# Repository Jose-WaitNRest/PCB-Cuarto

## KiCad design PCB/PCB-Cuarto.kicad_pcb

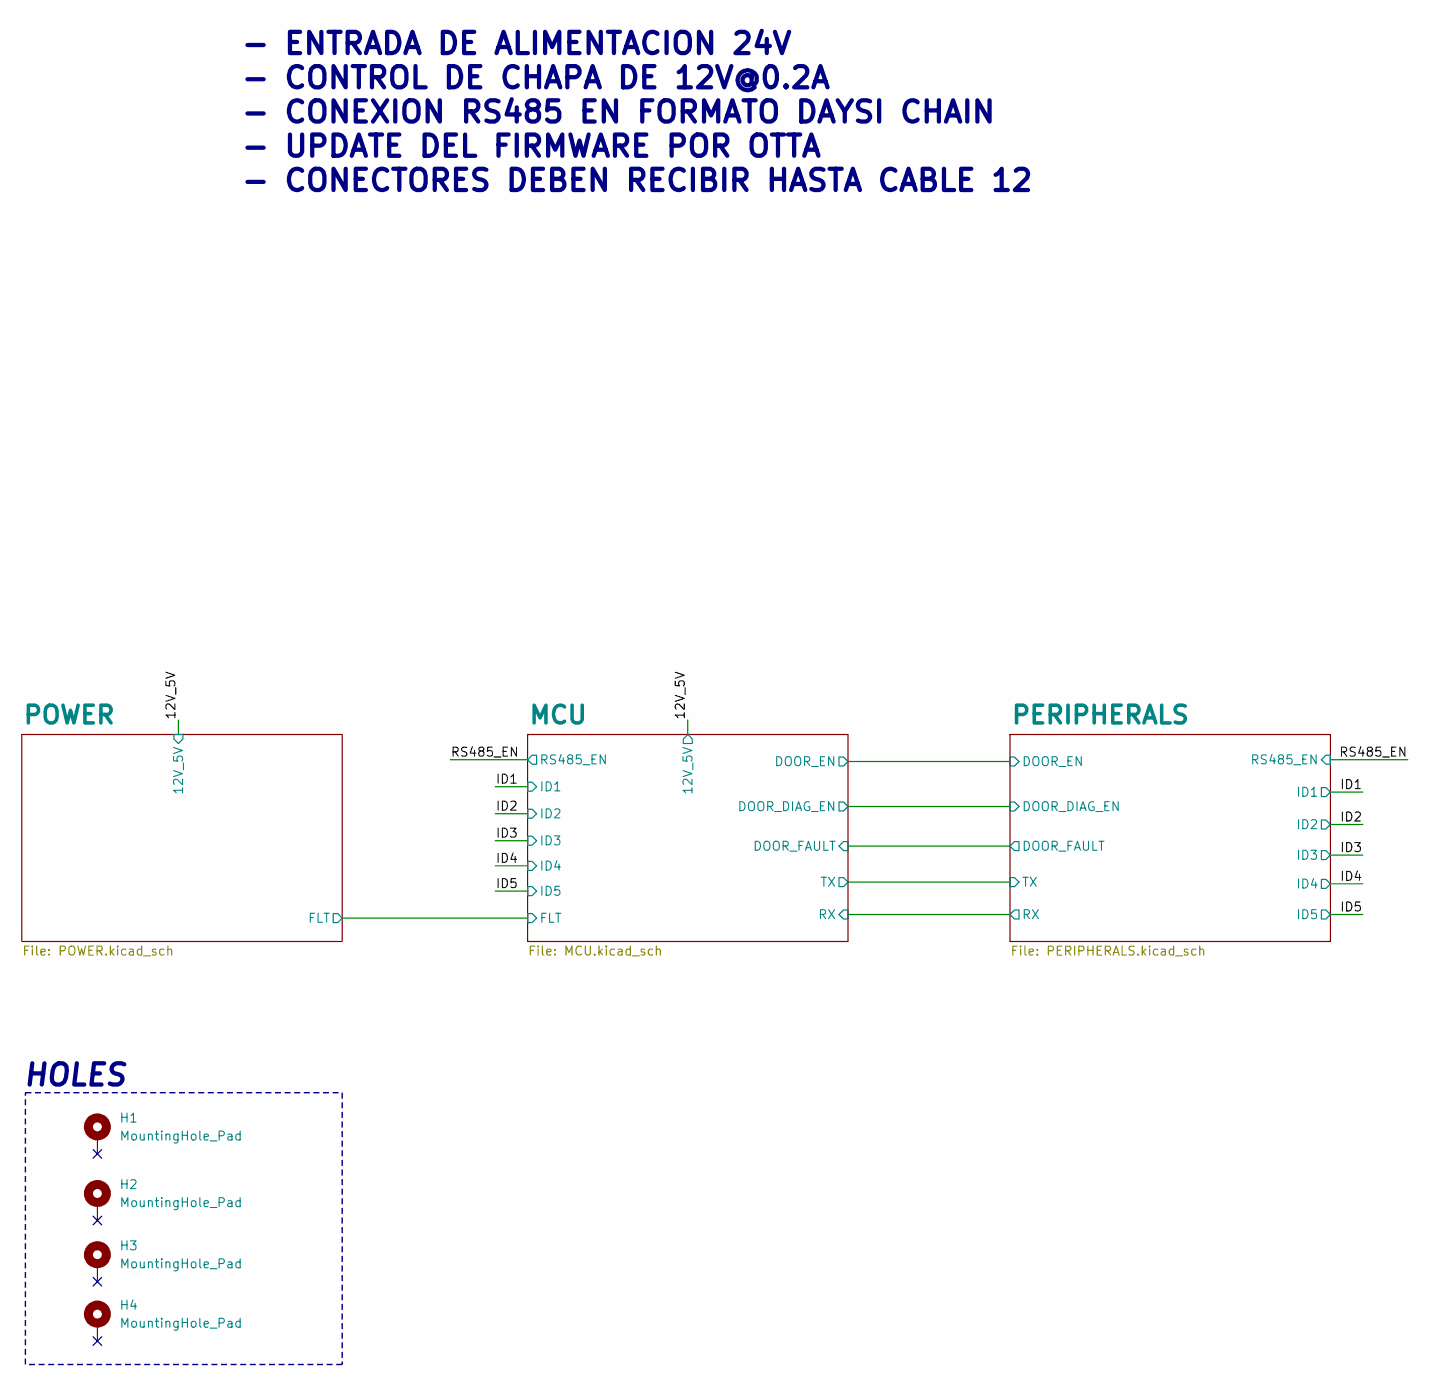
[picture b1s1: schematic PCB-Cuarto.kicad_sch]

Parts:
H1, H2, H3, H4: MountingHole_Pad; MountingHole_3.5mm_Pad_Via

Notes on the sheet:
- ENTRADA DE ALIMENTACION 24V - CONTROL DE CHAPA DE 12V@0.2A - CONEXION RS485 EN FORMATO DAYSI CHAIN - UPDATE DEL FIRMWARE POR OTTA - CONECTORES DEBEN RECIBIR HASTA CABLE 12
HOLES

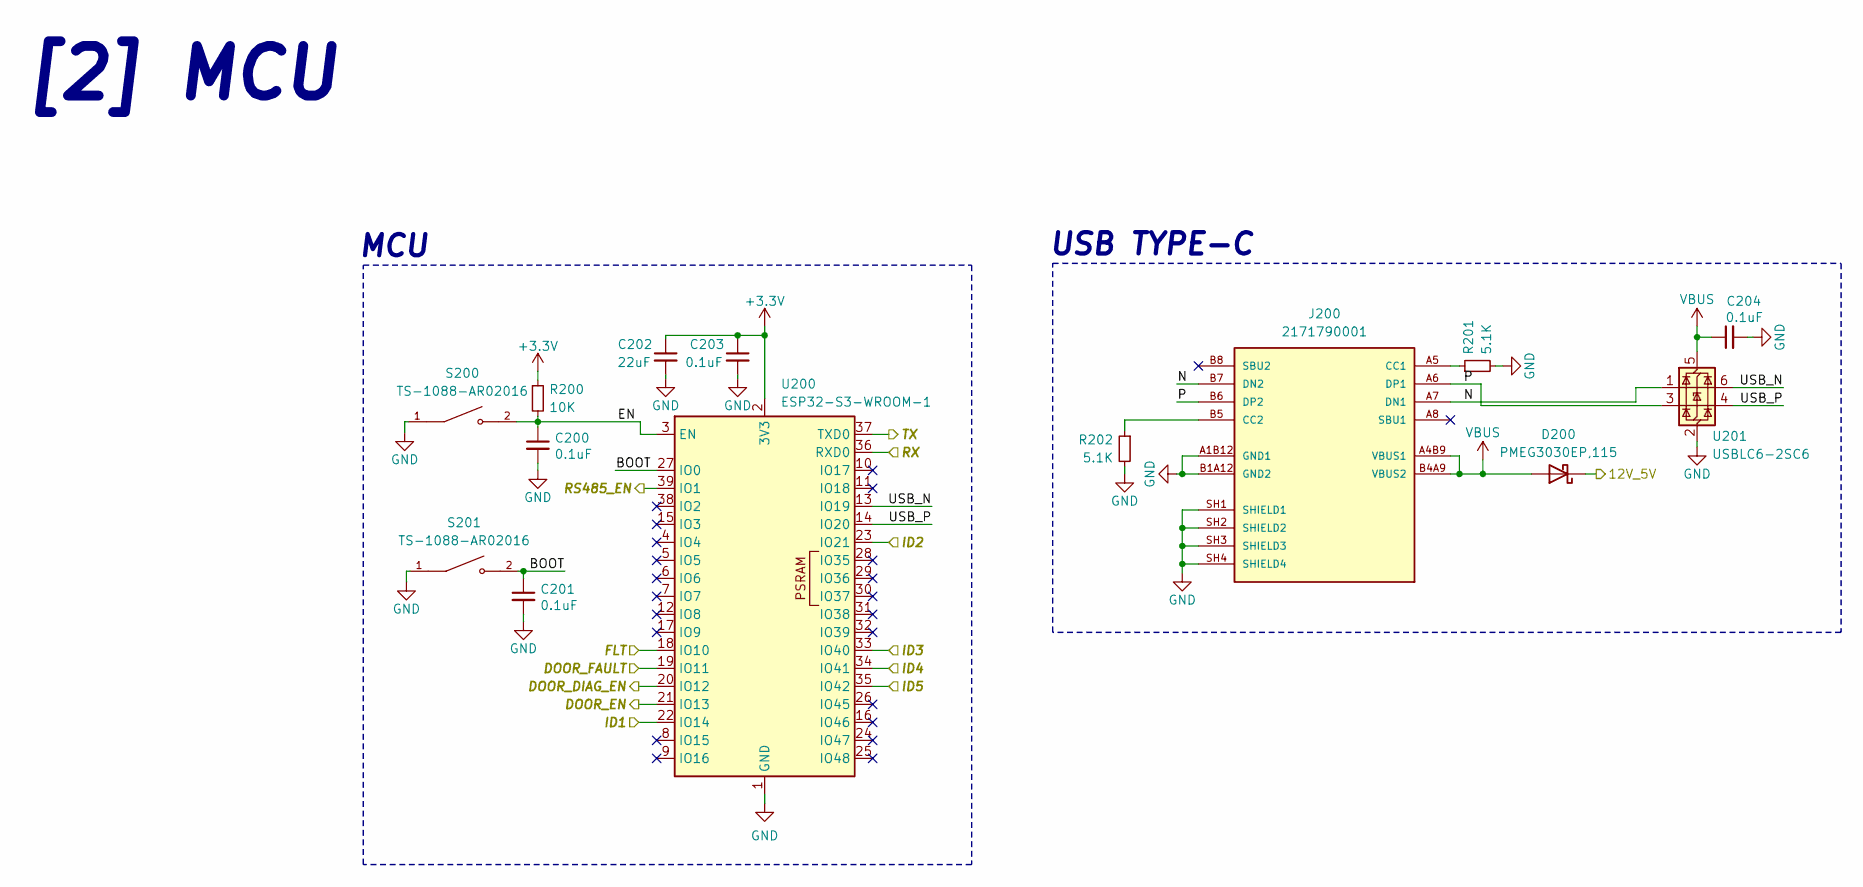
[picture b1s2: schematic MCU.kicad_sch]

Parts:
C200, C201, C203, C204: 0.1uF; C_0603_1608Metric_Pad1.08x0.95mm_HandSolder; LCSC C14663
C202: 22uF; C_0603_1608Metric_Pad1.08x0.95mm_HandSolder; LCSC C86295
D200: PMEG3030EP,115; D_SOD-128; LCSC C255587
J200: 2171790001; MOLEX_2171790001; LCSC C3197684
R200: 10K; R_0603_1608Metric; LCSC C25804
R201, R202: 5.1K; R_0603_1608Metric; LCSC C23186
S200, S201: TS-1088-AR02016; LCSC C720477
U200: ESP32-S3-WROOM-1; LCSC C2913202
U201: USBLC6-2SC6; SOT-23-6

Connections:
+3.3V: C202.1, C203.1, R200.1, U200.2 (3V3); also elsewhere on the board
/12V_5V: D200.1 (K); also elsewhere on the board
/ID1: U200.22 (IO14); also elsewhere on the board
/ID2: U200.23 (IO21); also elsewhere on the board
/ID3: U200.33 (IO40); also elsewhere on the board
/ID4: U200.34 (IO41); also elsewhere on the board
/ID5: U200.35 (IO42); also elsewhere on the board
/MCU/BOOT: C201.1, S201.2, U200.27 (IO0)
/MCU/DOOR_DIAG_EN: U200.20 (IO12); also elsewhere on the board
/MCU/DOOR_EN: U200.21 (IO13); also elsewhere on the board
/MCU/DOOR_FAULT: U200.19 (IO11); also elsewhere on the board
/MCU/EN: C200.1, R200.2, S200.2, U200.3 (EN)
/MCU/FLT: U200.18 (IO10); also elsewhere on the board
/MCU/N: J200.A7 (DN1), J200.B7 (DN2), U201.1 (I/O1)
/MCU/P: J200.A6 (DP1), J200.B6 (DP2), U201.3 (I/O2)
/MCU/RX: U200.36 (RXD0); also elsewhere on the board
/MCU/TX: U200.37 (TXD0); also elsewhere on the board
/MCU/USB_N: U200.13 (IO19), U201.6 (I/O1)
/MCU/USB_P: U200.14 (IO20), U201.4 (I/O2)
/RS485_EN: U200.39 (IO1); also elsewhere on the board
GND: C200.2, C201.2, C202.2, C203.2, C204.2, J200.A1B12 (GND1), J200.B1A12 (GND2), J200.SH1 (SHIELD1), J200.SH2 (SHIELD2), J200.SH3 (SHIELD3), J200.SH4 (SHIELD4), R201.2, R202.2, S200.1, S201.1, U200.1 (GND), U200.40 (GND), U200.41 (GND), U201.2 (GND); also elsewhere on the board
unnamed: J200.A5 (CC1), R201.1
unnamed: J200.B5 (CC2), R202.1
VBUS: C204.1, D200.2 (A), J200.A4B9 (VBUS1), J200.B4A9 (VBUS2), U201.5 (VBUS)

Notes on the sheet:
USB TYPE-C
[2] MCU
MCU

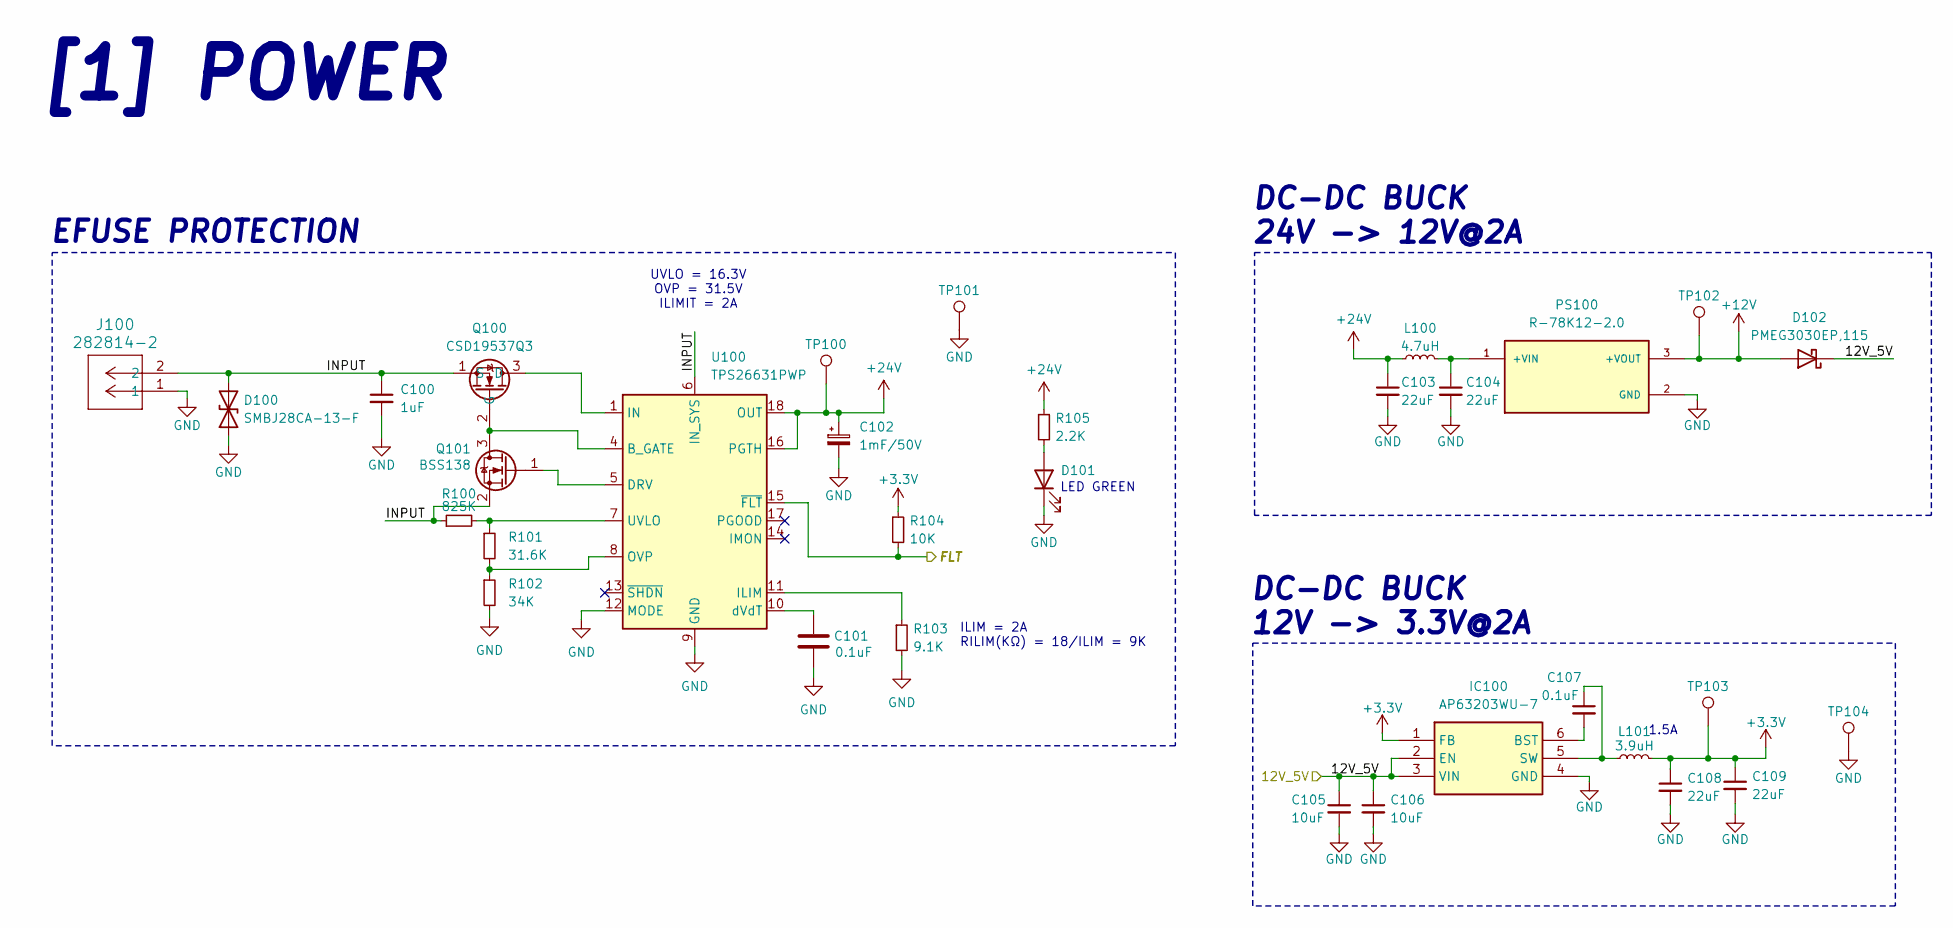
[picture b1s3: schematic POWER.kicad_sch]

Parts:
C100: 1uF; C_1206_3216Metric_Pad1.33x1.80mm_HandSolder; LCSC C1848
C101: 0.1uF; C_0603_1608Metric; LCSC C14663
C102: 1mF/50V; VKMI1701H102MV; LCSC C487374
C103, C104: 22uF; C_1206_3216Metric; LCSC C342620
C105, C106: 10uF; C_0805_2012Metric_Pad1.18x1.45mm_HandSolder; LCSC C440198
C107: 0.1uF; C_0603_1608Metric_Pad1.08x0.95mm_HandSolder; LCSC C14663
C108, C109: 22uF; C_0603_1608Metric_Pad1.08x0.95mm_HandSolder; LCSC C86295
D100: SMBJ28CA-13-F; D_SMB; LCSC C135064
D101: 19-21/GHC-YR1S2/4T; LED_0603_1608Metric; LCSC C2986048
D102: PMEG3030EP,115; D_SOD-128; LCSC C255587
IC100: AP63203WU-7; AP63203WU7; LCSC C780769
J100: 282814-2; LCSC C5187973
L100: 4.7uH; MDA5030-4R7M; LCSC C2847477
L101: 3.9uH; L_Sunlord_SWPA4030S; LCSC C96899
PS100: R-78K12-2.0; R-78K12-2_0; PARTREV 0/2023
Q100: CSD19537Q3; Mouser Part Number 595-CSD19537Q3
Q101: BSS138; SOT-23; LCSC C40912
R100: 825K; R_0805_2012Metric; LCSC C49010125
R101: 31.6K; R_0603_1608Metric; LCSC C25967
R102: 34K; R_0603_1608Metric; LCSC C23008
R103: 9.1K; R_0603_1608Metric; LCSC C23260
R104: 10K; R_0603_1608Metric; LCSC C25804
R105: 2.2K; R_0603_1608Metric; LCSC C4190
TP100, TP101, TP102, TP103, TP104: TestPoint; TestPoint_Pad_D2.0mm
U100: TPS26631PWP; HTSSOP-20-1EP_4.4x6.5mm_P0.65mm_EP3.4x6.5mm_Mask2.96x2.96mm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; LCSC C2832195

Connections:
+3.3V: C108.1, C109.1, IC100.1 (FB), L101.2, R104.1, TP103.1; also elsewhere on the board
+12V: D102.2 (A), PS100.3 (+VOUT), TP102.1; also elsewhere on the board
+24V: C102.1, C103.1, L100.1, R105.1, TP100.1, U100.16 (PGTH), U100.18 (OUT), U100.19 (OUT), U100.20 (OUT)
/12V_5V: C105.1, C106.1, D102.1 (K), IC100.2 (EN), IC100.3 (VIN); also elsewhere on the board
/MCU/FLT: R104.2, U100.15 (~FLT); also elsewhere on the board
/POWER/INPUT: C100.1, D100.2 (A2), J100.2, Q100.1 (S), Q101.2 (S), R100.1, U100.6 (IN_SYS)
GND: C100.2, C101.1, C102.2, C103.2, C104.2, C105.2, C106.2, C108.2, C109.2, D100.1 (A1), D101.1 (K), IC100.4 (GND), J100.1, PS100.2 (GND), R102.2, R103.2, TP101.1, TP104.1, U100.9 (GND), U100.12 (MODE), U100.21 (GND); also elsewhere on the board
unnamed: D101.2 (A), R105.2
unnamed: C107.2, IC100.6 (BST)
unnamed: C107.1, IC100.5 (SW), L101.1
unnamed: C104.1, L100.2, PS100.1 (+VIN)
unnamed: Q100.3 (D), U100.1 (IN), U100.2 (IN), U100.3 (IN)
unnamed: Q100.2 (G), Q101.3 (D), U100.4 (B_GATE)
unnamed: Q101.1 (G), U100.5 (DRV)
unnamed: R103.1, U100.11 (ILIM)
unnamed: R101.2, R102.1, U100.8 (OVP)
unnamed: R100.2, R101.1, U100.7 (UVLO)
unnamed: C101.2, U100.10 (dVdT)

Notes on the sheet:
[1] POWER
DC-DC BUCK 24V -> 12V@2A
DC-DC BUCK 12V -> 3.3V@2A
LED GREEN
UVLO = 16.3V OVP = 31.5V ILIMIT = 2A
EFUSE PROTECTION
ILIM = 2A RILIM(KΩ) = 18/ILIM = 9K
1.5A

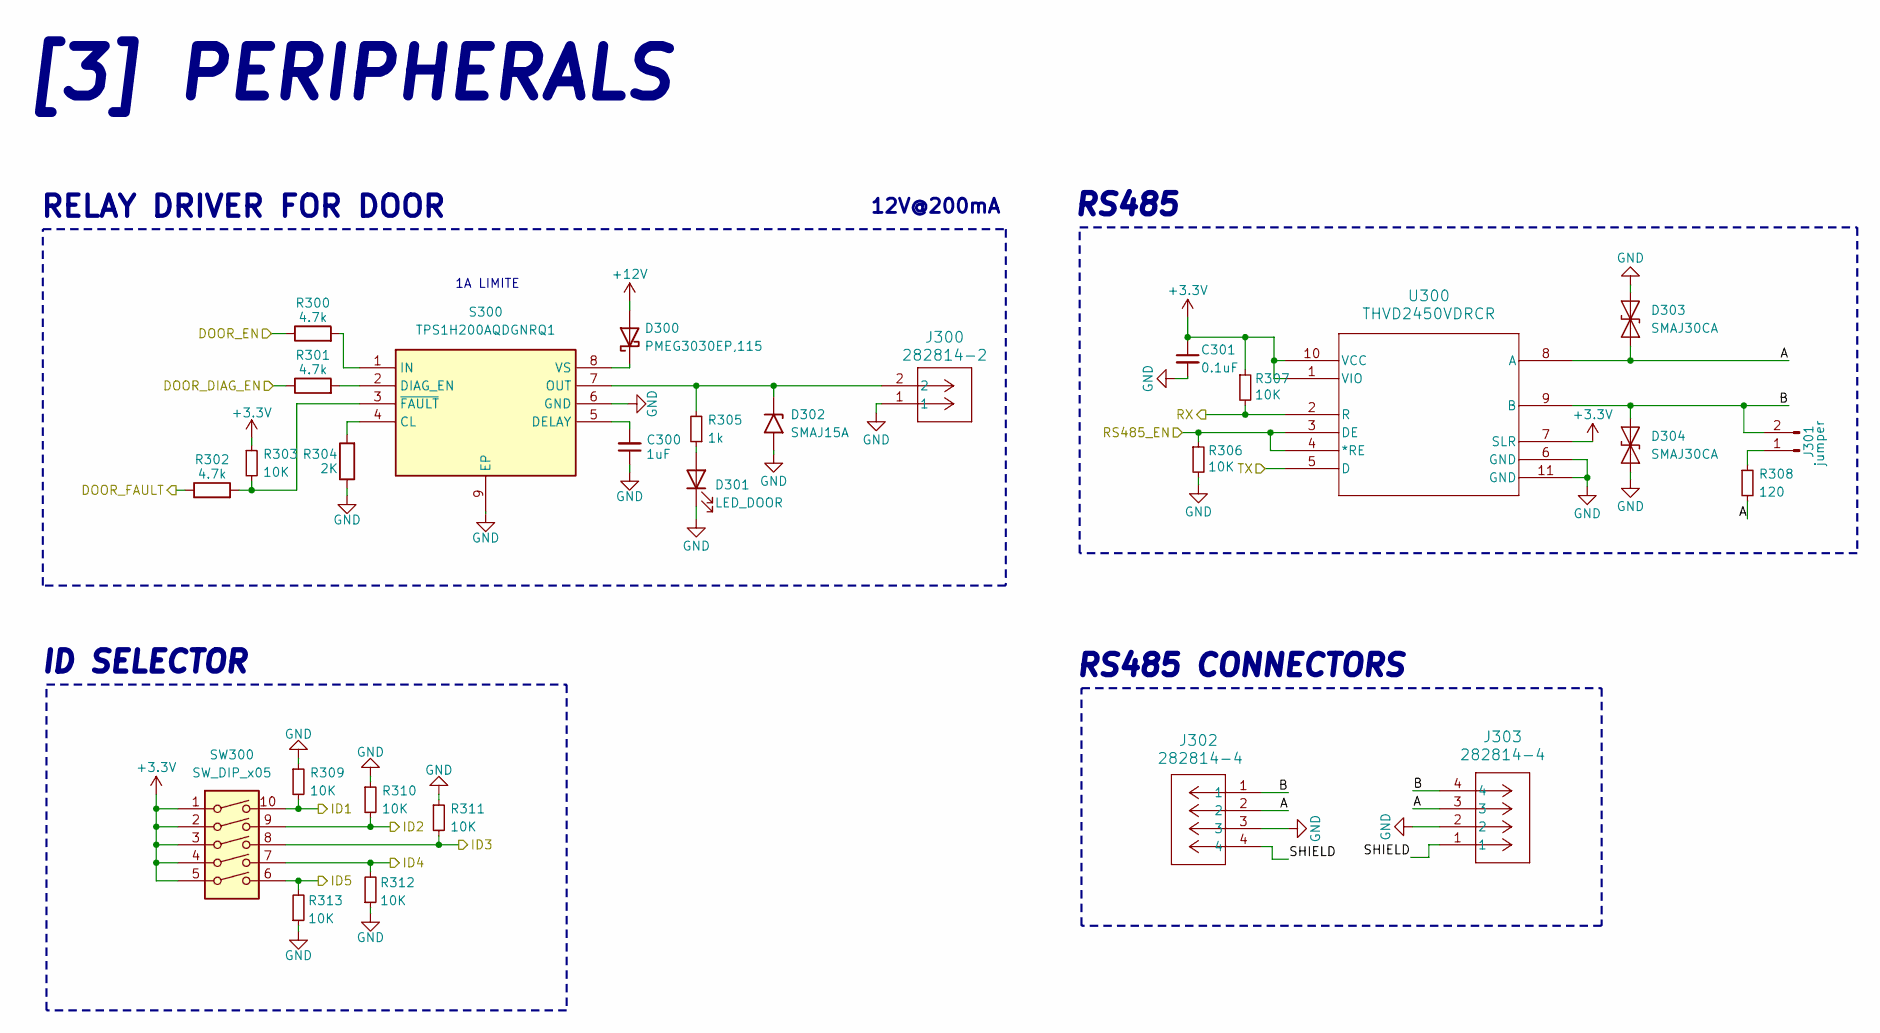
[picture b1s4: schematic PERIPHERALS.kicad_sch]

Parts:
C300: 1uF; C_0603_1608Metric_Pad1.08x0.95mm_HandSolder; LCSC C15849
C301: 0.1uF; C_0603_1608Metric; LCSC C14663
D300: PMEG3030EP,115; D_SOD-128; LCSC C255587
D301: LED_DOOR; LED_0603_1608Metric; LCSC C72038
D302: SMAJ15A; D_SMA; LCSC C110520
D303, D304: SMAJ30CA; D_SMA; LCSC C83322
J300: 282814-2; LCSC C5187973
J301: jumper; PinHeader_1x02_P2.54mm_Vertical; LCSC C492401
J302, J303: 282814-4; LCSC C5187975
R300, R301, R302: 4.7k; R_0603_1608Metric; LCSC C23162
R303, R306, R307, R309, R310, R311, R312, R313: 10K; R_0603_1608Metric; LCSC C25804
R304: 2K; R_0603_1608Metric; LCSC C22975
R305: 1k; R_0603_1608Metric; LCSC C21190
R308: 120; R_0603_1608Metric; LCSC C22787
S300: TPS1H200AQDGNRQ1; SOP65P490X110-9N; LCSC C2653785
SW300: SW_DIP_x05; DSIC-05-LS-GER; LCSC C7471367
U300: THVD2450VDRCR; VSON10_DRC_TEX; LCSC C5960705

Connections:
+3.3V: C301.1, R303.1, R307.1, SW300.1, SW300.2, SW300.3, SW300.4, SW300.5, U300.1 (VIO), U300.7 (SLR), U300.10 (VCC); also elsewhere on the board
+12V: D300.2 (A); also elsewhere on the board
/ID1: R309.2, SW300.10; also elsewhere on the board
/ID2: R310.2, SW300.9; also elsewhere on the board
/ID3: R311.2, SW300.8; also elsewhere on the board
/ID4: R312.2, SW300.7; also elsewhere on the board
/ID5: R313.2, SW300.6; also elsewhere on the board
/MCU/DOOR_DIAG_EN: R301.1; also elsewhere on the board
/MCU/DOOR_EN: R300.1; also elsewhere on the board
/MCU/DOOR_FAULT: R302.1; also elsewhere on the board
/MCU/RX: R307.2, U300.2 (R); also elsewhere on the board
/MCU/TX: U300.5 (D); also elsewhere on the board
/PERIPHERALS/A: D303.2 (A2), J302.2, J303.3, R308.2, U300.8 (A)
/PERIPHERALS/B: D304.2 (A2), J301.2, J302.1, J303.4, U300.9 (B)
/PERIPHERALS/SHIELD: J302.4, J303.1
/RS485_EN: R306.1, U300.3 (DE), U300.4 (*RE); also elsewhere on the board
GND: C300.1, C301.2, D301.1 (K), D302.2 (A2), D303.1 (A1), D304.1 (A1), J300.1, J302.3, J303.2, R304.1, R306.2, R309.1, R310.1, R311.1, R312.1, R313.1, S300.6 (GND), S300.9 (EP), U300.6 (GND), U300.11 (GND); also elsewhere on the board
unnamed: D300.1 (K), S300.8 (VS)
unnamed: D301.2 (A), R305.1
unnamed: D302.1 (A1), J300.2, R305.2, S300.7 (OUT)
unnamed: J301.1, R308.1
unnamed: R304.2, S300.4 (CL)
unnamed: C300.2, S300.5 (DELAY)
unnamed: R301.2, S300.2 (DIAG_EN)
unnamed: R300.2, S300.1 (IN)
unnamed: R302.2, R303.2, S300.3 (~FAULT)

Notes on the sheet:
ID SELECTOR
RS485 CONNECTORS
RELAY DRIVER FOR DOOR
[3] PERIPHERALS
1A LIMITE
12V@200mA
RS485

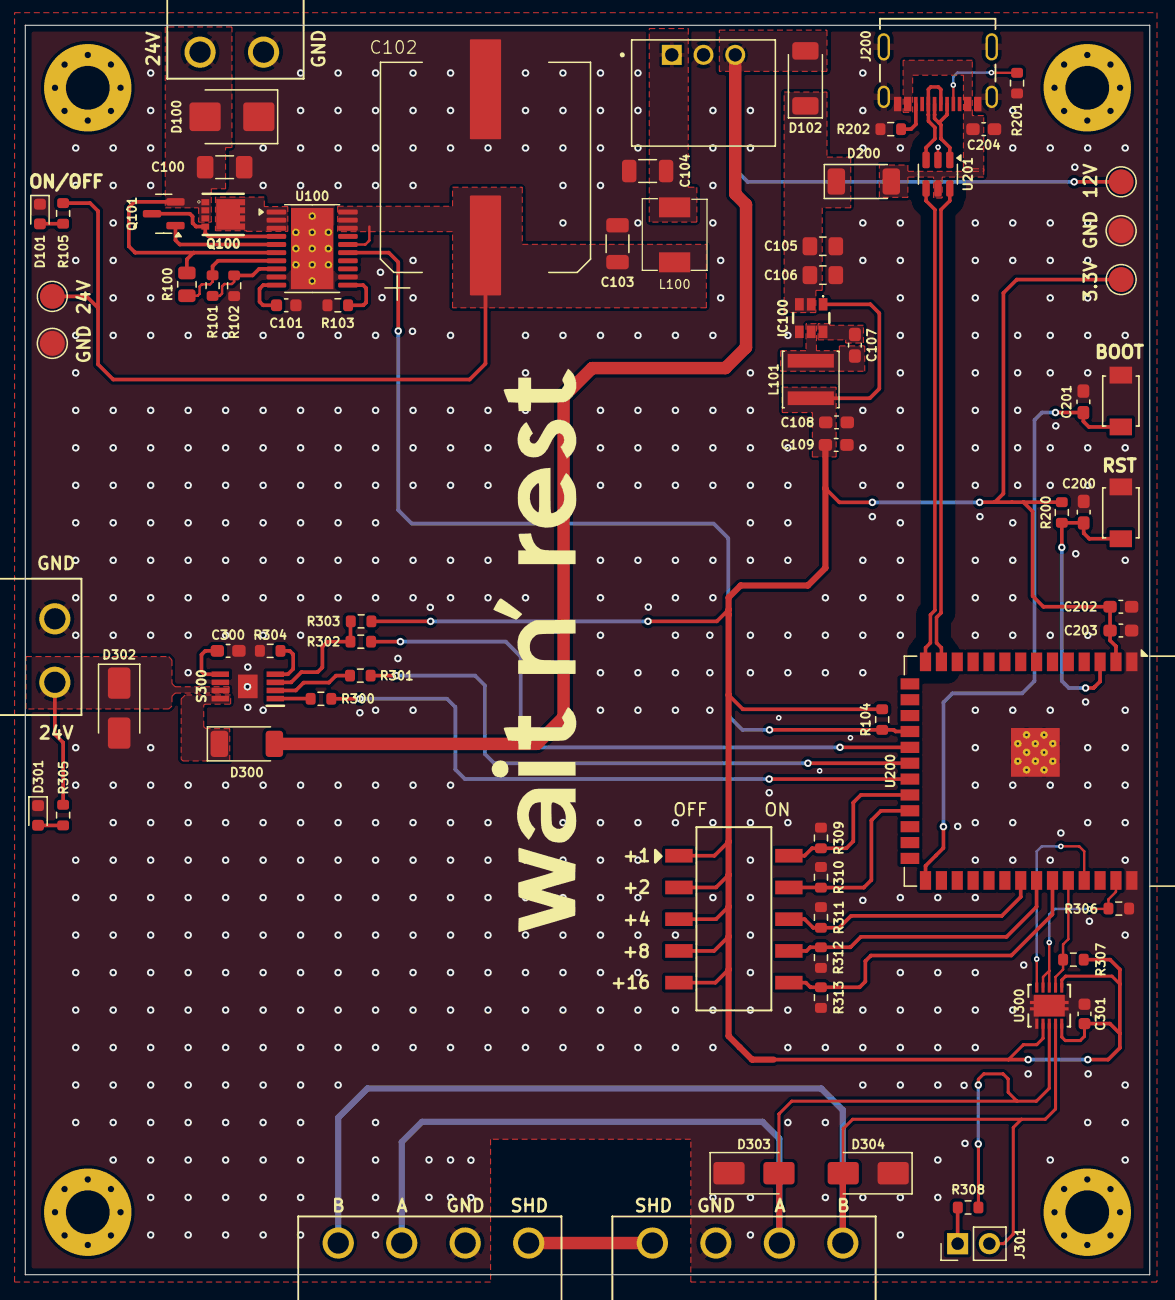
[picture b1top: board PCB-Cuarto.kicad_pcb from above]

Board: 4 copper layers, 90.0 x 100.0 mm, 78 parts (0 on the bottom side), 50 nets.

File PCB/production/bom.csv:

Designator,Footprint,Quantity,Value,LCSC Part #
C100,1206,1,1uF,C1848
"C101, C107, C200, C201, C203, C204, C301",0603,7,0.1uF,C14663
C102,VKMI1701H102MV,1,1mF/50V,C487374
"C103, C104",1206,2,22uF,C342620
"C105, C106",0805,2,10uF,C440198
"C108, C109, C202",0603,3,22uF,C86295
C300,0603,1,1uF,C15849
D100,D_SMB,1,SMBJ28CA-13-F,C135064
D101,0603,1,19-21/GHC-YR1S2/4T,C2986048
"D102, D200, D300",D_SOD-128,3,"PMEG3030EP,115",C255587
D301,0603,1,LED_DOOR,C72038
D302,D_SMA,1,SMAJ15A,C110520
"D303, D304",D_SMA,2,SMAJ30CA,C83322
IC100,AP63203WU7,1,AP63203WU-7,C780769
J100,2604-3102,1,2604-3102,
J200,MOLEX_2171790001,1,2171790001,C3197684
"J201, J302, J303",2086-1104-THT,3,2086-1104,
J300,2086-1102-THT,1,2086-1102,
J301,PinHeader_1x02_P2.54mm_Vertical,1,jumper,C492401
L100,MDA5030-4R7M,1,4.7uH,C2847477
L101,L_Sunlord_SWPA4030S,1,3.9uH,C96899
PS100,R-78K12-2_0,1,R-78K12-2.0,
Q100,CSD19537Q3,1,CSD19537Q3,C478469
Q101,SOT-23,1,BSS138,C40912
R100,0805,1,825K,C49010125
R101,0603,1,31.6K,C25967
R102,0603,1,34K,C23008
R103,0603,1,9.1K,C23260
"R104, R200, R303, R306, R307, R309, R310, R311, R312, R313",0603,10,10K,C25804
R105,0603,1,2.2K,C4190
"R201, R202",0603,2,5.1K,C23186
"R300, R301, R302",0603,3,4.7k,C23162
R304,0603,1,2K,C22975
R305,0603,1,1k,C21190
R308,0603,1,120,C22787
"S200, S201",TS-1187A-B-A-B,2,TS-1187A-B-A-B,C318884
S300,SOP65P490X110-9N,1,TPS1H200AQDGNRQ1,C2653785
SW300,DSIC-05-LS-GER,1,SW_DIP_x05,C7471367
"TP100, TP101, TP102, TP103, TP104",TestPoint_Pad_D2.0mm,5,TestPoint,
U100,HTSSOP-20-1EP_4.4x6.5mm_P0.65mm_EP3.4x6.5mm_Mask2.96x2.96mm_ThermalVias,1,TPS26631PWP,C2832195
U200,ESP32-S3-WROOM-1,1,ESP32-S3-WROOM-1,C2913202
U201,SOT-23-6,1,USBLC6-2SC6,
U300,VSON10_DRC_TEX,1,THVD2450VDRCR,C5960705

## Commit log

2026-03-04 Creación del ecosistema de trabajo
    Se creo el ecosistema de trabajo de la PCB y además, el file KICAD de la PCB
2026-03-05 Implementacion del eFuse
    Se hizo el diseño esquematico del eFuse
2026-03-05 Diseño DC-DC
    Se diseño las 2 etapas DC-DC:
    - 24V a 12V con filtros
    - 12V a 3.3V
2026-03-05 Diseño MCU ESP32-S3 y USB-C conector
    Se diseño el ESP32-S3-WROOM-1 junto a su conector USB-C para flashear el MCU
2026-03-08 Agregado RS485, Smart Switch, ORING Diode
    Se termino de acabar todo el esquematico, solo falta crear el footprint para un inductor
2026-03-10 Placement
    Se termino de crear el footprint para el inductor y placement en la PCB
2026-03-16 PCB acabada con labels
    Se agrego:
    - Planos de tierra
    - Stitching vias
    - Labels indicadores para todo los conectores
    Se corrigio:
    - Errores de librerias de footprint - TPS26631RGE
2026-03-16 Edicion de archivos para JLCPCB
    Se ha realizado:
    - Cambio de footprint de capacitor 1mF
    - Edicion de algunos value references
    - Creación de archivos para JLCPCB
2026-03-18 Fix label conector RS485
    El label del conector RS485 estaba erroneo, se tuvo que cambiar las posiciones
2026-04-05 Mejora en ruteo
    - Se ha mejorado el ruteo de potencia
    - Se ha generado los files para JLCPCB
2026-04-06 Cambio de footprint del eFuse
    - Se cambio el footprint del eFuse debido a que el actual no hay stock en JLCPCB
    - Se creo de nuevo los archivos de configuracion de JLCPCB
2026-04-07 Fix Stitching Vias y Clearance USB trace
    * Se eliminaron las vías que se encontraban demasiado cercanas a componentes o a ciertas zonas, lo cual representaba un problema común generado por el uso de *stitching vias*.
    * Se definió un *clearance* de 0.8 mm para las pistas USB, con el fin de respetar el cálculo de impedancia bajo una configuración *no coplanar*. Esto se debe a que, al estar la PCB completamente rode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
2026-04-07 fix gitignore
2026-04-22 Change Placement
    Se ha cambiado el placement total para obtener una mejor posicion de conexion de los perifericos
